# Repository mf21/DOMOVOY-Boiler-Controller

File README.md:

# DOMOVOY Boiler Controller
This device is a part of DOMOVOY home automation project

https://www.mf21.ru

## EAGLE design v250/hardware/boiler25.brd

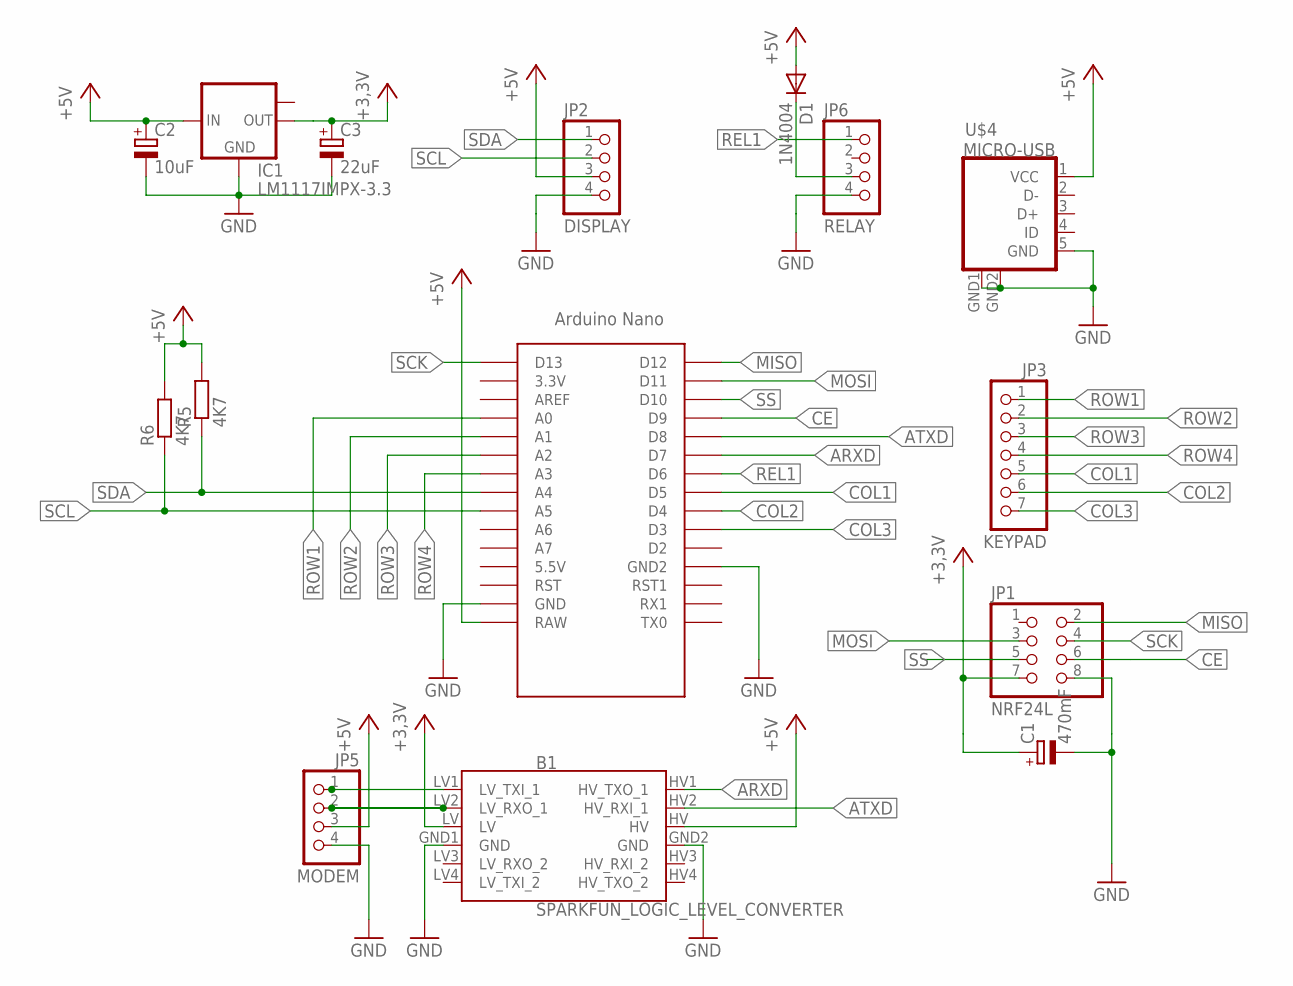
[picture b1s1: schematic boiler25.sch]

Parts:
B1: SPARKFUN_LOGIC_LEVEL_CONVERTER
C1: 470mF; E3,5-8
C2: 10uF; E1,8-4
C3: 22uF; E1,8-4
D1: 1N4004; DO41-10
IC1: LM1117IMPX-3.3; SOT223
JP1: NRF24L; 2X04
JP2: DISPLAY; 1X04
JP3: KEYPAD; 1X07
JP5: MODEM; 1X04
JP6: RELAY; 1X04
R5, R6: 4K7; M1206
U$4: MICRO-USB
U$5: NANO

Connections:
+3,3V: B1.LV, C1.+, C3.+, IC1.2 (OUT), JP1.7
+5V: B1.HV, C2.+, D1.A, IC1.3 (IN), JP2.3, JP5.3, R5.2, R6.2, U$4.1 (VCC), U$5.RAW
ARXD: B1.HV1 (HV_TXO_1), U$5.D7
ATXD: B1.HV2 (HV_RXI_1), U$5.D8
CE: JP1.6, U$5.D9
COL1: JP3.5, U$5.D5
COL2: JP3.6, U$5.D4
COL3: JP3.7, U$5.D3
GND: B1.GND1 (GND), B1.GND2 (GND), C1.-, C2.-, C3.-, IC1.1 (GND), JP1.8, JP2.4, JP5.4, JP6.4, U$4.5 (GND), U$4.GND1 (GND), U$4.GND2 (GND), U$5.GND, U$5.GND1 (GND2)
MISO: JP1.2, U$5.D12
MOSI: JP1.3, U$5.D11
unnamed: B1.LV1 (LV_TXI_1), JP5.1
unnamed: D1.C, JP6.3
unnamed: B1.LV2 (LV_RXO_1), JP5.2
REL1: JP6.1, U$5.D6
ROW1: JP3.1, U$5.A0
ROW2: JP3.2, U$5.A1
ROW3: JP3.3, U$5.A2
ROW4: JP3.4, U$5.A3
SCK: JP1.4, U$5.D13
SCL: JP2.2, R6.1, U$5.A5
SDA: JP2.1, R5.1, U$5.A4
SS: JP1.5, U$5.D10

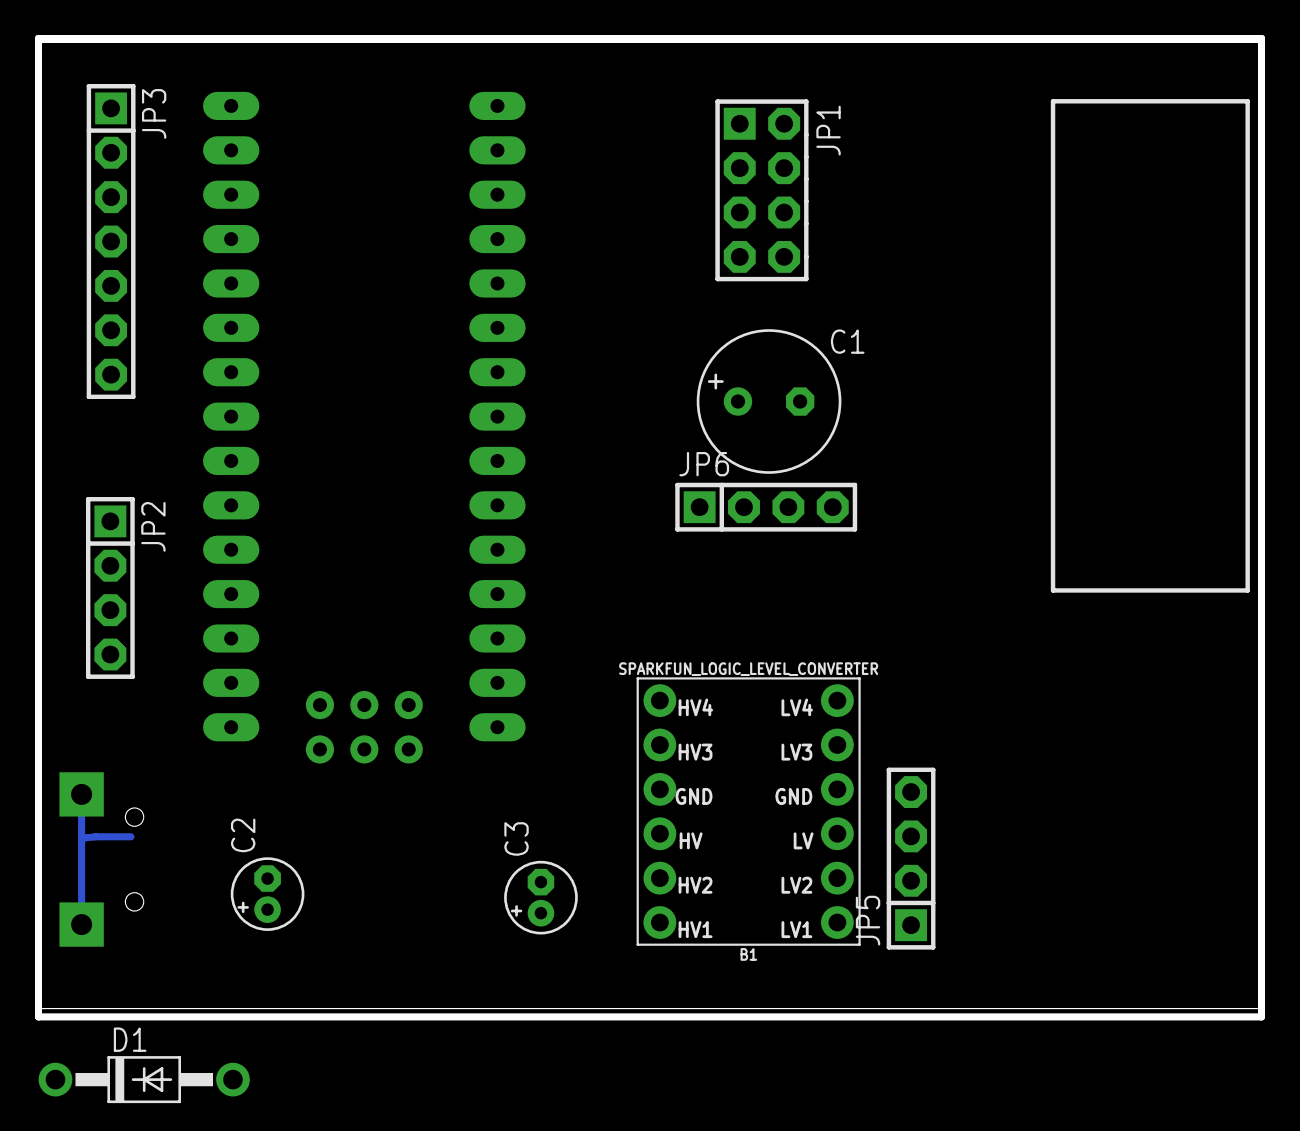
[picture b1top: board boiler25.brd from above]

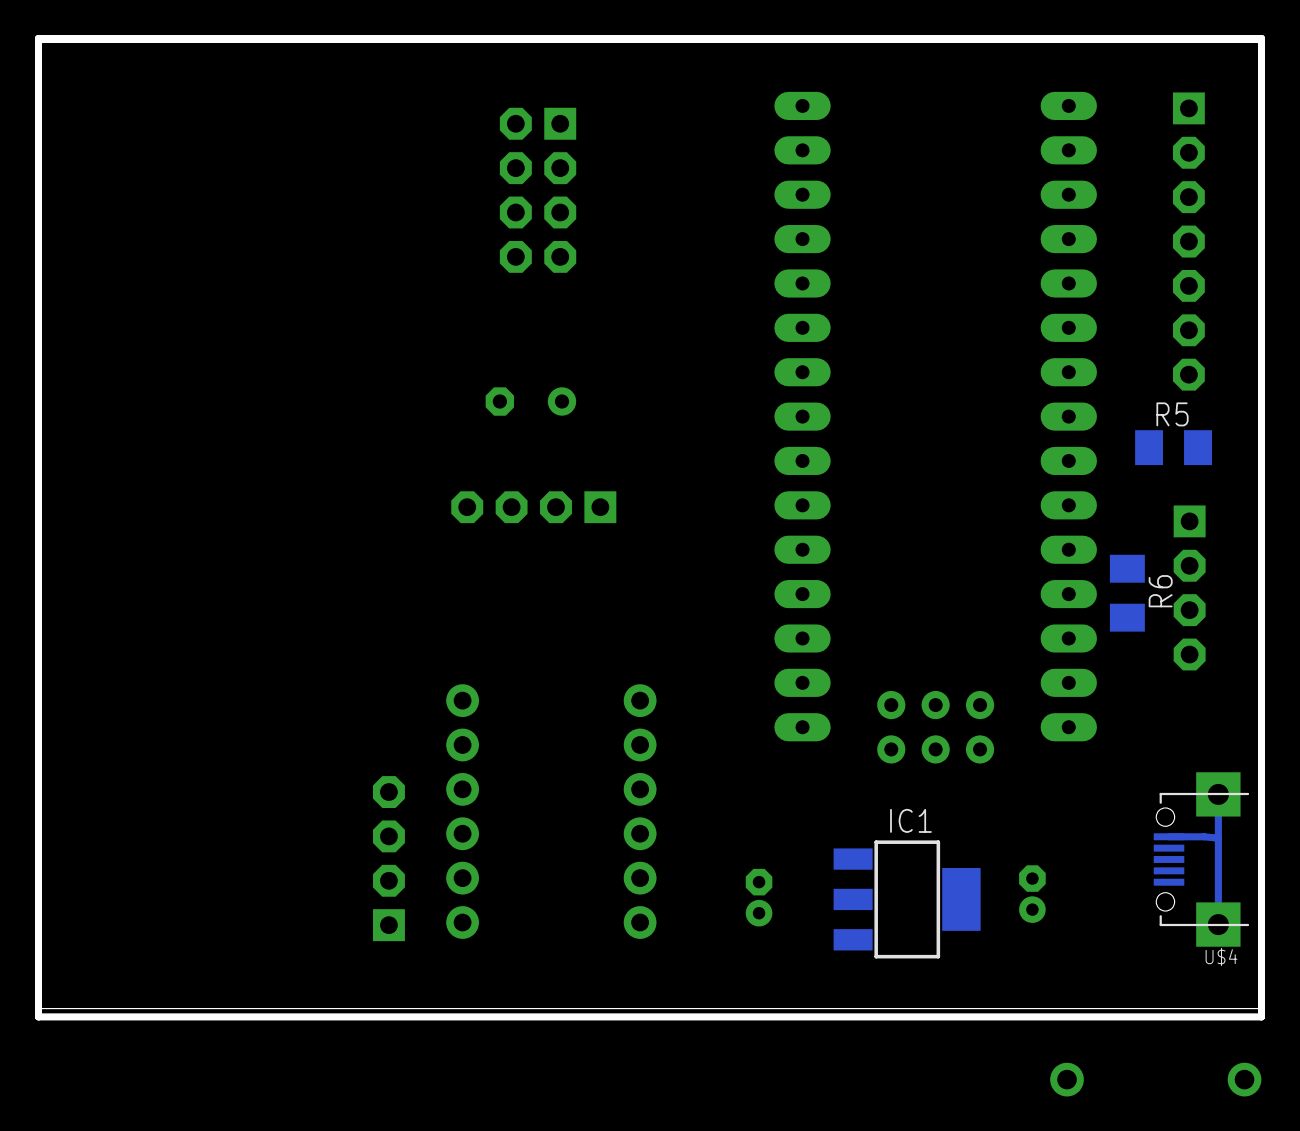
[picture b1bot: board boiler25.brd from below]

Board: 2 copper layers, 70.0 x 56.0 mm, 15 parts (4 on the bottom side), 23 nets.

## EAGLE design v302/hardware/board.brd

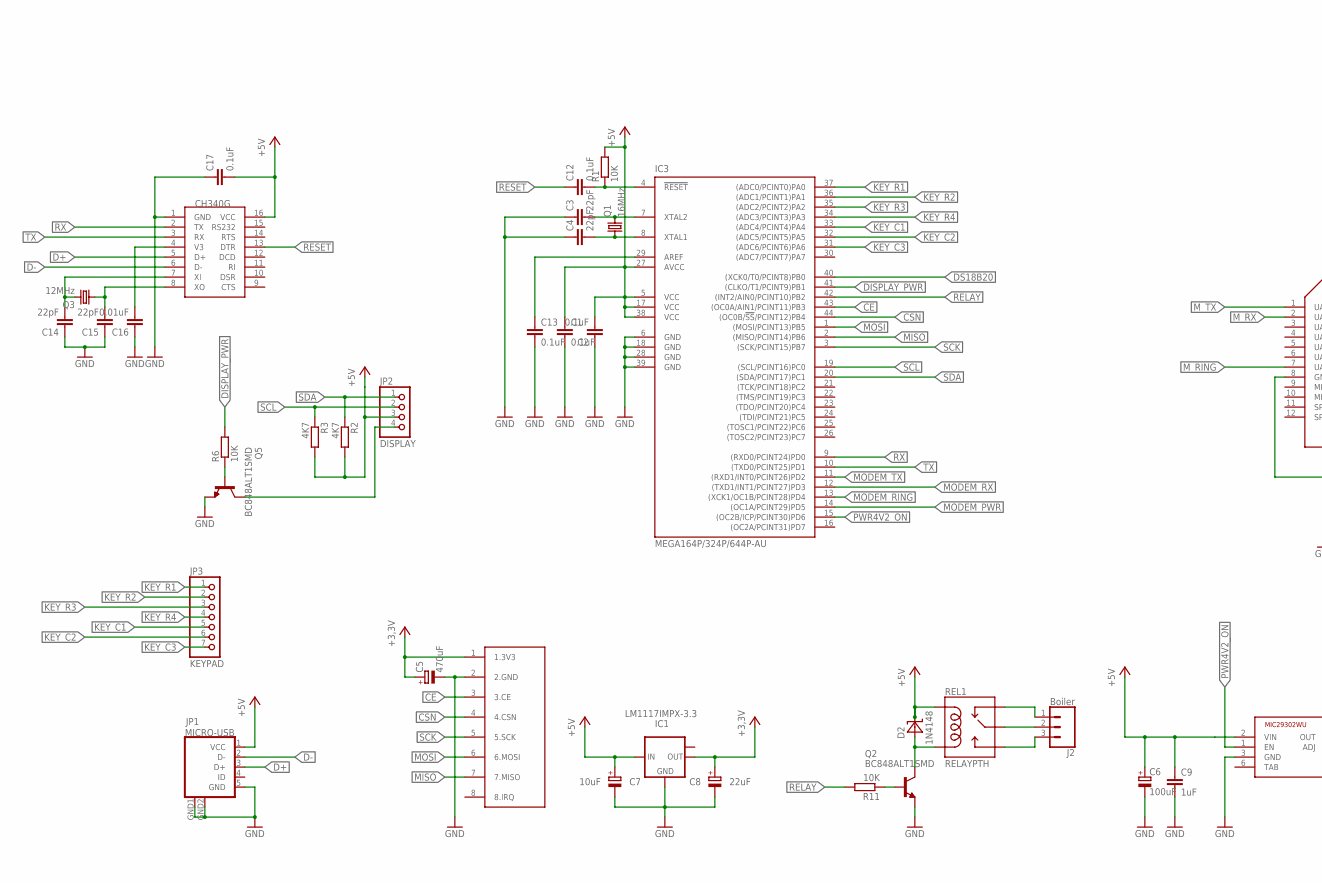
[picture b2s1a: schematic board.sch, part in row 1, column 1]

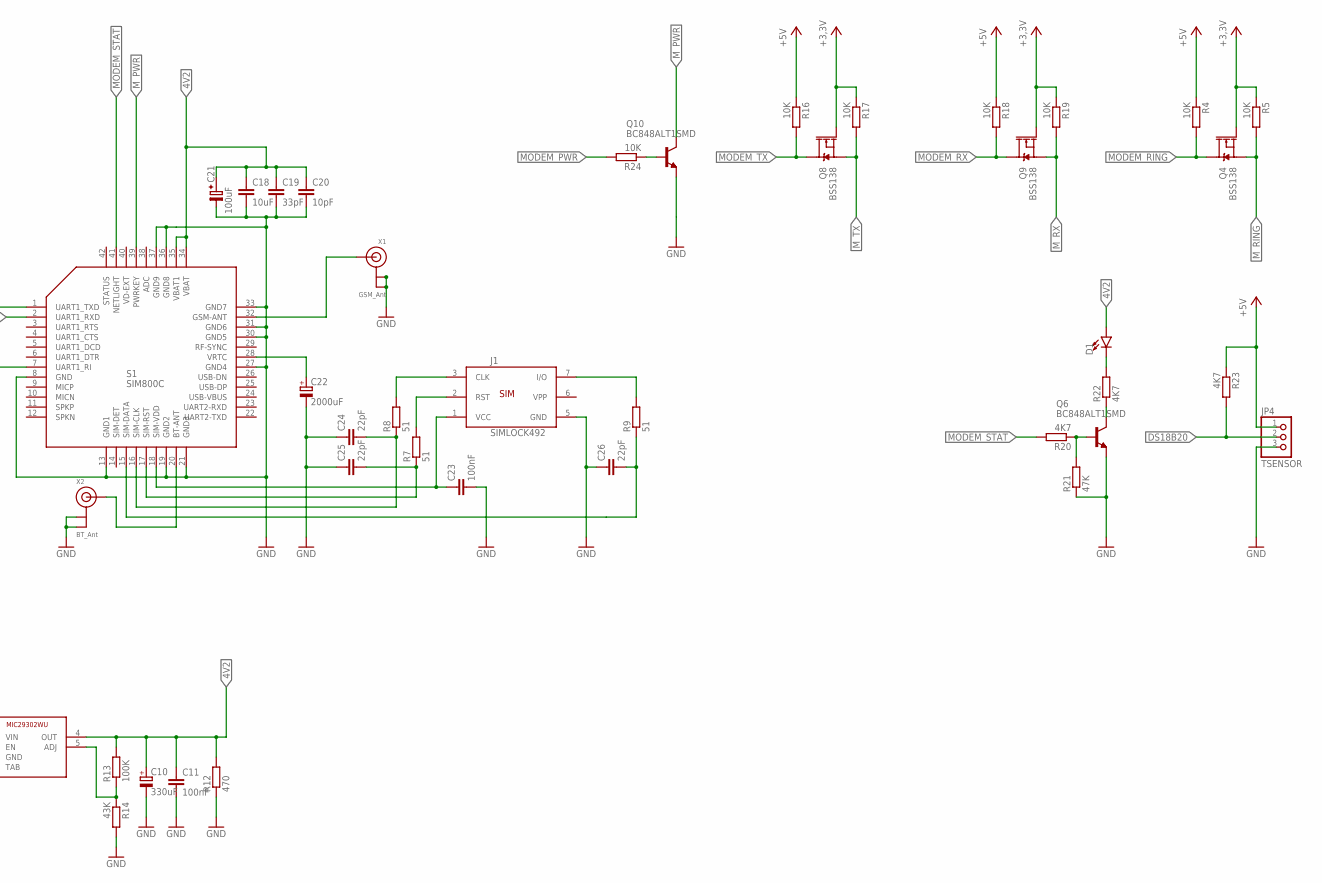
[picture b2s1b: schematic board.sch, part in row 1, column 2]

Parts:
C1, C2, C12, C13, C17: 0.1uF; C1206
C3, C4, C14, C15, C24, C25, C26: 22pF; C1206
C5: 470uF; E3,5-8
C6: 100uF; E1,8-4
C7: 10uF; E1,8-4
C8: 22uF; E1,8-4
C9: 1uF; C1206
C10: 330uF; E1,8-4
C11, C23: 100nF; C1206
C16: 0.01uF; C1206
C18: 10uF; C1206
C19: 33pF; C1206
C20: 10pF; C1206
C21: 100uF; TE-D-7343
C22: 2000uF; E3,5-8
D1: LED1206; LED-1206
D2: 1N4148; SOD323-W
IC1: LM1117IMPX-3.3; SOT223
IC2: MIC29302WU; TO263-5
IC3: MEGA164P/324P/644P-AU; TQFP44
J1: SIMLOCK492; 5002
J2: Boiler; SCREWTERMINAL-5MM-3
JP1: MICRO-USB
JP2: DISPLAY; 1X04
JP3: KEYPAD; 1X07
JP4: TSENSOR; 1X03
Q1: 16MHz; HC49/S
Q2, Q5, Q6, Q10: BC848ALT1SMD; SOT23
Q3: 12MHz; HC49/S
Q4, Q8, Q9: BSS138; SOT23-3
R1, R4, R5, R6, R11, R16, R17, R18, R19, R24: 10K; R1206
R2, R3, R20, R22, R23: 4K7; R1206
R7, R8, R9: 51; R1206
R12: 470; R1206
R13: 100K; R1206
R14: 43K; R1206
R21: 47K; R1206
REL1: RELAYPTH; SRD-05VDC-SL-C
S1: SIM800C
U$1: CH340G; SOIC16
U$3: NRF24L01+
X1: GSM_Ant; U.FL
X2: BT_Ant; U.FL

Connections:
4V2: C10.+, C11.1, C18.1, C19.1, C20.1, C21.+, D1.A, IC2.4 (OUT), R12.2, R13.2, S1.34 (VBAT), S1.35 (VBAT1)
+3,3V: C5.+, C8.+, IC1.2 (OUT), Q4.1 (G), Q8.1 (G), Q9.1 (G), R5.1, R17.1, R19.1, U$3.1 (1.3V3)
+5V: C1.1, C2.2, C6.+, C7.+, C9.1, C17.2, D2.C, IC1.3 (IN), IC2.2 (VIN), IC3.5 (VCC), IC3.17 (VCC), IC3.27 (AVCC), IC3.38 (VCC), JP1.1 (VCC), JP2.3, JP4.1, R1.2, R2.2, R3.2, R4.1, R16.1, R18.1, R23.1, REL1.COIL1, U$1.16 (VCC)
CE: IC3.43 ((OC0A/AIN1/PCINT11)PB3), U$3.3 (3.CE)
CSN: IC3.44 ((OC0B/!SS!/PCINT12)PB4), U$3.4 (4.CSN)
D+: JP1.3 (D+), U$1.5 (D+)
D-: JP1.2 (D-), U$1.6 (D-)
DISPLAY_PWR: IC3.41 ((CLKO/T1/PCINT9)PB1), R6.2
DS18B20: IC3.40 ((XCK0/T0/PCINT8)PB0), JP4.2, R23.2
GND: C1.2, C2.1, C3.1, C4.1, C5.-, C6.-, C7.-, C8.-, C9.2, C10.-, C11.2, C13.2, C14.1, C15.1, C16.1, C17.1, C18.2, C19.2, C20.2, C21.-, C22.-, C23.2, C24.1, C25.1, C26.1, IC1.1 (GND), IC2.3 (GND), IC3.6 (GND), IC3.18 (GND), IC3.28 (GND), IC3.39 (GND), J1.5 (GND), JP1.5 (GND), JP1.GND1 (GND), JP1.GND2 (GND), JP4.3, Q2.2 (E), Q5.2 (E), Q6.2 (E), Q10.2 (E), R12.1, R14.2, R21.1, S1.8 (GND), S1.13 (GND1), S1.19 (GND2), S1.21 (GND3), S1.27 (GND4), S1.30 (GND5), S1.31 (GND6), S1.33 (GND7), S1.36 (GND8), S1.37 (GND9), U$1.1 (GND), U$3.2 (2.GND), X1.1 (GND), X1.2 (GND), X2.1 (GND), X2.2 (GND)
KEY_C1: IC3.33 ((ADC4/PCINT4)PA4), JP3.5
KEY_C2: IC3.32 ((ADC5/PCINT5)PA5), JP3.6
KEY_C3: IC3.31 ((ADC6/PCINT6)PA6), JP3.7
KEY_R1: IC3.37 ((ADC0/PCINT0)PA0), JP3.1
KEY_R2: IC3.36 ((ADC1/PCINT1)PA1), JP3.2
KEY_R3: IC3.35 ((ADC2/PCINT2)PA2), JP3.3
KEY_R4: IC3.34 ((ADC3/PCINT3)PA3), JP3.4
MISO: IC3.2 ((MISO/PCINT14)PB6), U$3.7 (7.MISO)
MODEM_PWR: IC3.14 ((OC1A/PCINT29)PD5), R24.2
MODEM_RING: IC3.13 ((XCK1/OC1B/PCINT28)PD4), Q4.3 (D), R4.2
MODEM_RX: IC3.12 ((TXD1/INT1/PCINT27)PD3), Q9.3 (D), R18.2
MODEM_STAT: R20.2, S1.41 (NETLIGHT)
MODEM_TX: IC3.11 ((RXD1/INT0/PCINT26)PD2), Q8.3 (D), R16.2
MOSI: IC3.1 ((MOSI/PCINT13)PB5), U$3.6 (6.MOSI)
M_PWR: Q10.3 (C), S1.39 (PWRKEY)
M_RING: Q4.2 (S), R5.2, S1.7 (UART1_RI)
M_RX: Q9.2 (S), R19.2, S1.2 (UART1_RXD)
M_TX: Q8.2 (S), R17.2, S1.1 (UART1_TXD)
unnamed: C3.2, IC3.7 (XTAL2), Q1.2
unnamed: C4.2, IC3.8 (XTAL1), Q1.1
unnamed: C13.1, IC3.29 (AREF)
unnamed: C12.2, IC3.4 (!RESET), R1.1
unnamed: C14.2, Q3.2, U$1.7 (XI)
unnamed: C15.2, Q3.1, U$1.8 (XO)
unnamed: JP2.4, Q5.3 (C)
unnamed: Q5.1 (B), R6.1
unnamed: C16.2, U$1.4 (V3)
unnamed: C22.+, S1.28 (VRTC)
unnamed: C23.1, J1.1 (VCC), S1.18 (SIM-VDD)
unnamed: D2.A, Q2.3 (C), REL1.COIL0
unnamed: Q2.1 (B), R11.1
unnamed: J2.1, REL1.SWCLOSED (SWCLOSE)
unnamed: J2.2, REL1.SWCOMMON
unnamed: J2.3, REL1.SWOPEN
unnamed: C25.2, R7.1, S1.17 (SIM-RST)
unnamed: J1.2 (RST), R7.2
unnamed: IC2.5 (ADJ), R13.1, R14.1
unnamed: C24.2, R8.1, S1.16 (SIM-CLK)
unnamed: J1.3 (CLK), R8.2
unnamed: C26.2, R9.1, S1.15 (SIM-DATA)
unnamed: J1.7 (I/O), R9.2
unnamed: S1.32 (GSM-ANT), X1.3 (SIGNAL)
unnamed: Q6.1 (B), R20.1, R21.2
unnamed: Q6.3 (C), R22.1
unnamed: D1.C, R22.2
unnamed: S1.20 (BT-ANT), X2.3 (SIGNAL)
unnamed: Q10.1 (B), R24.1
PWR4V2_ON: IC2.1 (EN), IC3.15 ((OC2B/ICP/PCINT30)PD6)
RELAY: IC3.42 ((INT2/AIN0/PCINT10)PB2), R11.2
RESET: C12.1, U$1.13 (DTR)
RX: IC3.9 ((RXD0/PCINT24)PD0), U$1.2 (TX)
SCK: IC3.3 ((SCK/PCINT15)PB7), U$3.5 (5.SCK)
SCL: IC3.19 ((SCL/PCINT16)PC0), JP2.2, R3.1
SDA: IC3.20 ((SDA/PCINT17)PC1), JP2.1, R2.1
TX: IC3.10 ((TXD0/PCINT25)PD1), U$1.3 (RX)

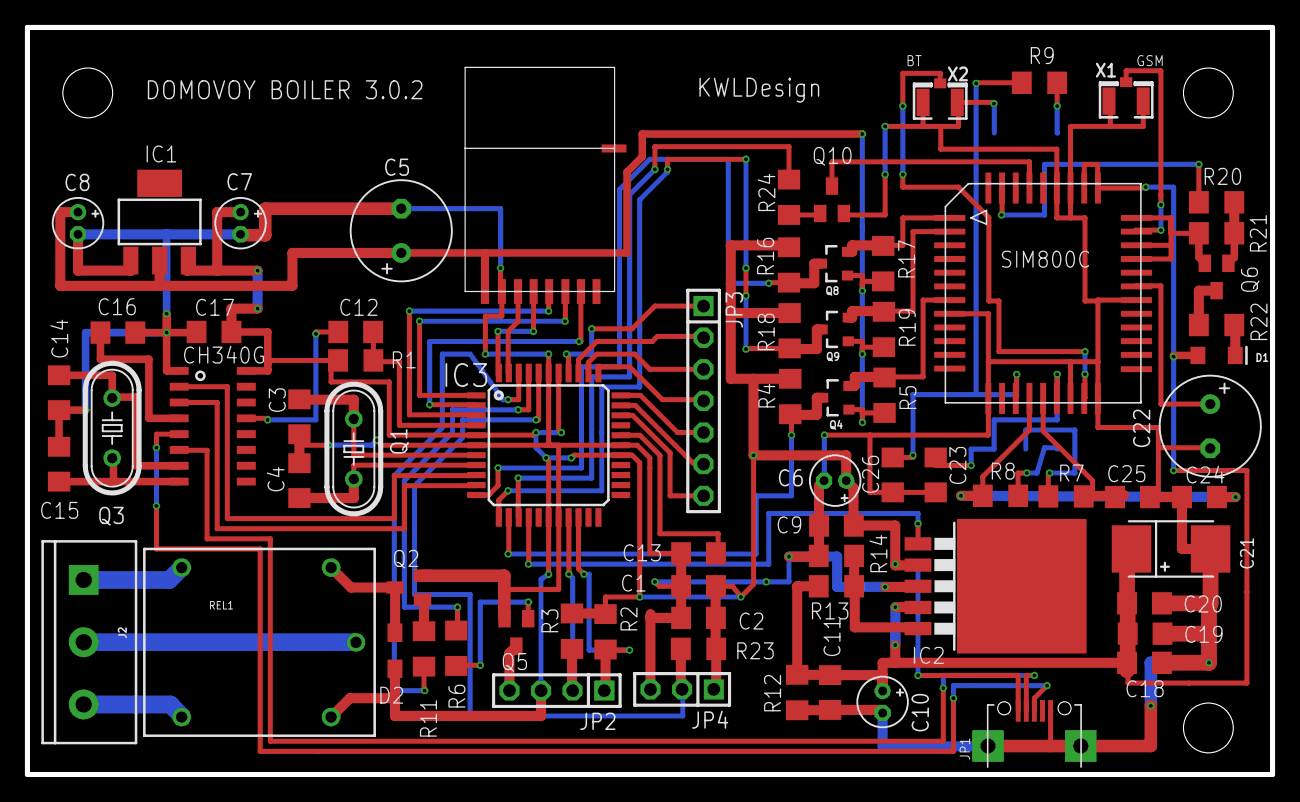
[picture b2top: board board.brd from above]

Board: 2 copper layers, 100.0 x 60.0 mm, 74 parts (1 on the bottom side), 65 nets.

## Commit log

2018-02-05 Version 2.52
    Fixed errors due modem startup
    Some remarks was deleted
2018-02-25 Readme change
2018-06-10 Old files ordered
2018-06-10 Folder software added

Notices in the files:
parts and their libraries:
SparkFun-Boards: Licensing: Creative Commons ShareAlike 4.0 International - https://creativecommons.org/licenses/by-sa/4.0
cap-pan40: Copyright (C) 2004, Bob Starr
